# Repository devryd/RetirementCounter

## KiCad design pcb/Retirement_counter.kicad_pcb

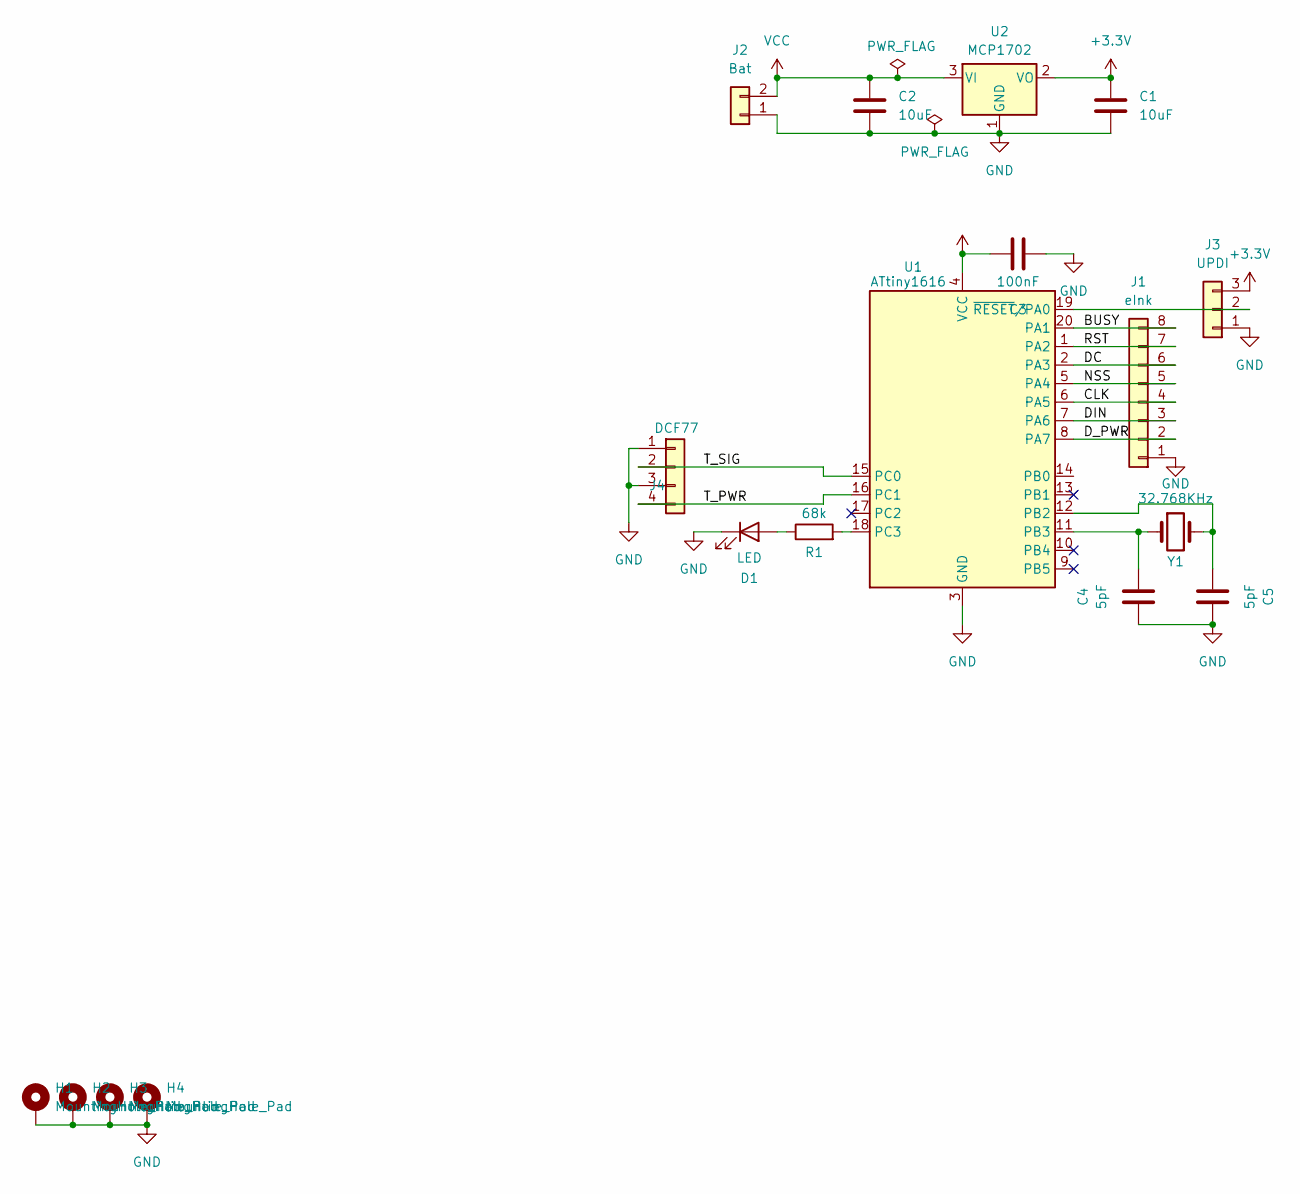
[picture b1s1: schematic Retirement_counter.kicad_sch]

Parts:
C1, C2: 10uF; C_0603_1608Metric
C3: 100nF; C_0603_1608Metric
C4, C5: 5pF; C_0603_1608Metric
D1: LED; LED_0603_1608Metric
H1, H2, H3, H4: MountingHole_Pad; MountingHole_2.5mm_Pad
J1: eInk; PinHeader_1x08_P2.54mm_Vertical
J2: Bat; PinHeader_1x02_P2.54mm_Vertical
J3: UPDI; PinHeader_1x03_P2.54mm_Vertical
J4: DCF77; PinHeader_1x04_P2.54mm_Vertical
R1: 68k; R_0402_1005Metric
U1: ATtiny1616; VQFN-20-1EP_3x3mm_P0.4mm_EP1.7x1.7mm_ThermalVias
U2: MCP1702; SOT-23
Y1: 32.768KHz; Crystal_C38-LF_D3.0mm_L8.0mm_Vertical

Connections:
+3.3V: C1.1, C3.2, J3.3, U1.4 (VCC), U2.2 (VO)
/BUSY: J1.8, U1.20 (PA1)
/CLK: J1.4, U1.6 (PA5)
/DC: J1.6, U1.2 (PA3)
/DIN: J1.3, U1.7 (PA6)
/D_PWR: J1.2, U1.8 (PA7)
/NSS: J1.5, U1.5 (PA4)
/RST: J1.7, U1.1 (PA2)
/T_PWR: J4.4, U1.16 (PC1)
/T_SIG: J4.2, U1.15 (PC0)
GND: C1.2, C2.2, C3.1, C4.1, C5.2, D1.1 (K), H1.1, H2.1, H3.1, H4.1, J1.1, J2.1, J3.1, J4.1, J4.3, U1.3 (GND), U1.21 (GND), U2.1 (GND)
unnamed: D1.2 (A), R1.1
unnamed: J3.2, U1.19 (~RESET/PA0)
unnamed: C5.1, U1.12 (PB2), Y1.2
unnamed: C4.2, U1.11 (PB3), Y1.1
unnamed: R1.2, U1.18 (PC3)
VCC: C2.1, J2.2, U2.3 (VI)

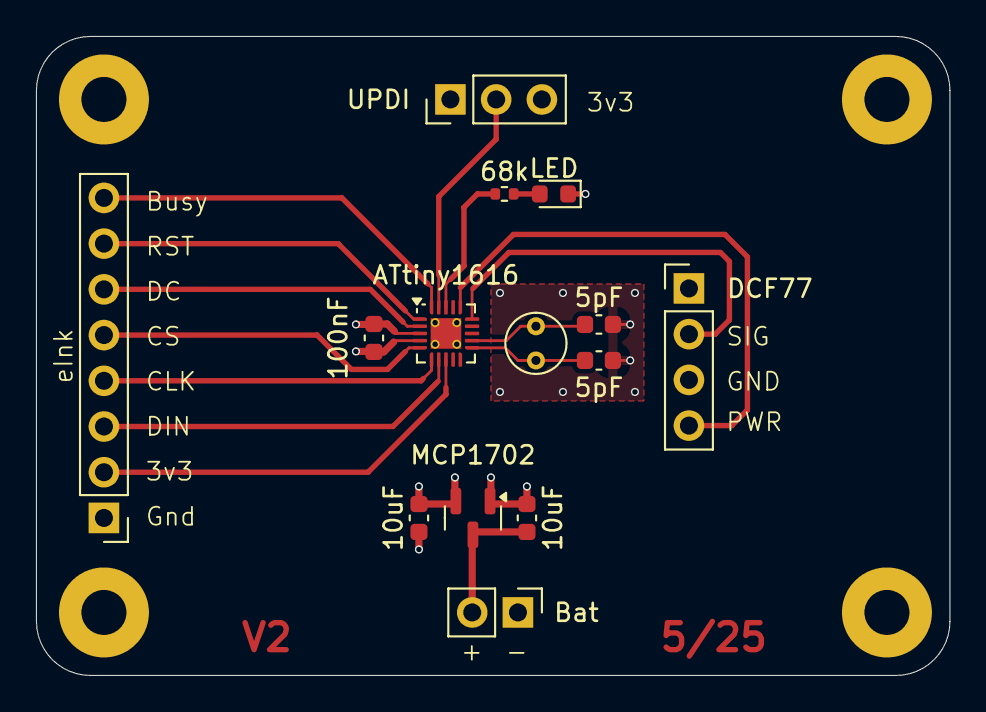
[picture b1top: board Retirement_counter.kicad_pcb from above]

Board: 6 copper layers, 50.8 x 35.5 mm, 18 parts (0 on the bottom side), 17 nets.

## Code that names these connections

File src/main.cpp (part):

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#include "time.h"

/*
PA7     D_PWR
PA6     SDA
PA5     SCL
PA4     CS
PA3     D/C
PA2     RST
PA1     BSY

PC0     DCF_SIG
PC1     DCF_PWR

PC3     LED

PB4     U_BAT

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
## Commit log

2025-01-20 feat: first commit
2025-01-20 feat: changed pins to new pcb
2025-01-24 feat: low power test with new board
2025-01-24 fix: fixed typo in platformio.ini
2025-01-27 feat: added struct tm functionality, improved power consumption
2025-01-31 feat: added write_days(), improved data write speed
2025-01-31 fix: toggle LED on first dcf read, to indicate signal reception
2025-02-01 feat: added bat monitoring, fixed month difference
2025-02-01 feat: added schematic and pcb layout
